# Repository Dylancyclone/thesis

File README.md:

# Building a Mobile Device that Leverages the Power of a Desktop Computer

## ASU Barrett Undergraduate Thesis 2022

## [READ THE PAPER HERE](./paper/small.pdf)

(Alternatively, [see it on asu.edu](https://keep.lib.asu.edu/items/165594))

Watch a timelapse of the paper here: https://youtu.be/VJ2HCxnmA_Y

## Abstract

With the recent focus of attention towards remote work and mobile computing, the possibility of taking a powerful workstation wherever needed is enticing.
However, even emerging laptops today struggle to compete with desktops in terms of cost, maintenance, and future upgrades.
The price point of a powerful laptop is considerably higher compared to an equally powerful desktop computer, and most laptops are manufactured in a way that makes upgrading parts of the machine difficult or impossible, forcing a complete purchase in the event of failure or a component needing an upgrade.

In the case where someone already owns a desktop computer and must be mobile, instead of needing to purchase a second device at full price, it may be possible to develop a low-cost computer that has just enough power to connect to the existing desktop and run all processing there, using the mobile device only as a user interface.

This thesis will explore the development of a custom PCB that utilizes a Raspberry Pi Computer Module 4, as well as the development of a fork of the Open Source project Moonlight to stream a host machine's screen to a remote client.
This implementation will be compared against other existing remote desktop solutions to analyze it's performance and quality.

## Information

This repository contains all the files and resources used to produce my Honors Thesis.

Folders are self-explanatory.

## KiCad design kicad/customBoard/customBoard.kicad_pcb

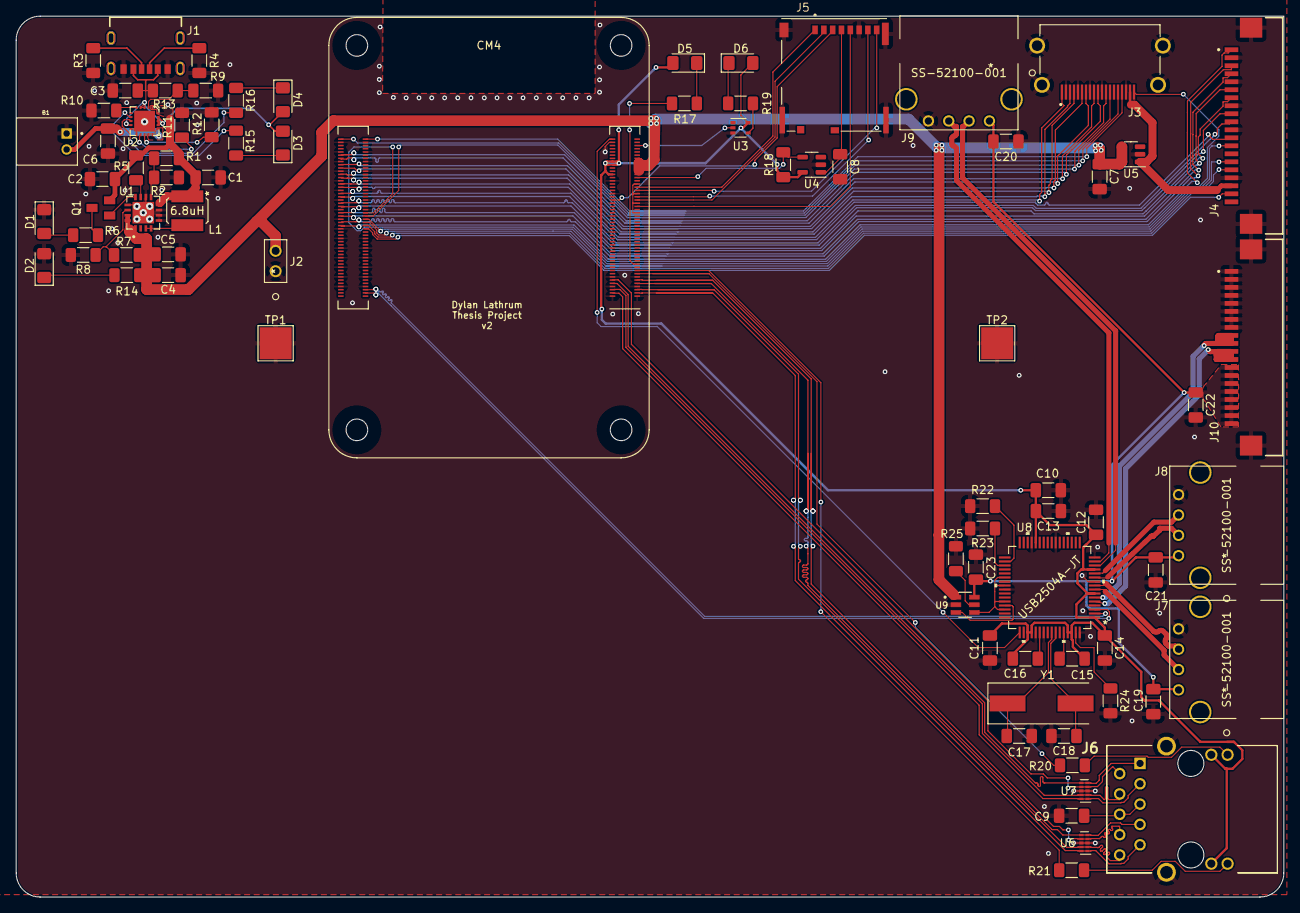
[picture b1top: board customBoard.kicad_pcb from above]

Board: 2 copper layers, 158.3 x 110.0 mm, 80 parts (0 on the bottom side), 98 nets.

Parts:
B1: JST 2-PH; JST_S2B-PH-K-S(LF)(SN)
C1, C3, C6: 10uF; C_1206_3216Metric_Pad1.33x1.80mm_HandSolder
C2: 0.1uF; C_1206_3216Metric_Pad1.33x1.80mm_HandSolder
C4: 2.2uF; C_1206_3216Metric_Pad1.33x1.80mm_HandSolder
C5, C23: 100uF; C_1206_3216Metric_Pad1.33x1.80mm_HandSolder
C7, C9, C12, C13, C14: 100n; C_1206_3216Metric_Pad1.33x1.80mm_HandSolder
C8, C10, C11, C19, C20, C21, C22: 10u; C_1206_3216Metric_Pad1.33x1.80mm_HandSolder
C15, C16: 4.7uF; C_1206_3216Metric_Pad1.33x1.80mm_HandSolder
C17, C18: 27pF; C_1206_3216Metric_Pad1.33x1.80mm_HandSolder
CM4: ComputeModule4-CM4; Raspberry-Pi-4-Compute-Module
D1, D2, D6: Red; LED_1206_3216Metric_Pad1.42x1.75mm_HandSolder
D3, D5: Green; LED_1206_3216Metric_Pad1.42x1.75mm_HandSolder
D4: Orange; LED_1206_3216Metric_Pad1.42x1.75mm_HandSolder
J1: USB4125-GF-A_REVA2; GCT_USB4125-GF-A_REVA2
J2: PREC002SAAN-RC
J3: SS-53000-001; STEWART_SS-53000-001
J4, J10: FFC3B07-20-T; GCT_FFC3B07-20-T
J5: Micro_SD_Card_Det; SDCARD_MOLEX_503398-1892
J6: ARJM11D7-502-AB-EW2; ARJM11D7502ABEW2
J7, J8, J9: SS-52100-001
L1: 6.8uH; NRS5030T6R8MMGJ
Q1: MMUN2133LT1G; SOT95P240X111-3N
R1, R7: 1.87M; R_1206_3216Metric_Pad1.30x1.75mm_HandSolder
R2: 340k; R_1206_3216Metric_Pad1.30x1.75mm_HandSolder
R3, R4: 5.1k; R_1206_3216Metric_Pad1.30x1.75mm_HandSolder
R5, R8: 200k; R_1206_3216Metric_Pad1.30x1.75mm_HandSolder
R6, R14, R17, R19: 1k; R_1206_3216Metric_Pad1.30x1.75mm_HandSolder
R9, R11: 100k; R_1206_3216Metric_Pad1.30x1.75mm_HandSolder
R10: 15k; R_1206_3216Metric_Pad1.30x1.75mm_HandSolder
R12: 1.0k; R_1206_3216Metric_Pad1.30x1.75mm_HandSolder
R13: 270k; R_1206_3216Metric_Pad1.30x1.75mm_HandSolder
R15, R16: 1K; R_1206_3216Metric_Pad1.30x1.75mm_HandSolder
R18: 12k 1%; R_1206_3216Metric_Pad1.30x1.75mm_HandSolder
R20, R21: 470R; R_1206_3216Metric_Pad1.30x1.75mm_HandSolder
R22, R23: 36K 1%; R_1206_3216Metric_Pad1.30x1.75mm_HandSolder
R24: 12K 1%; R_1206_3216Metric_Pad1.30x1.75mm_HandSolder
R25: 15K 1%; R_1206_3216Metric_Pad1.30x1.75mm_HandSolder
TP1, TP2: TestPoint; TestPoint_Pad_4.0x4.0mm
U1: TPS61090RSAR; QFN65P400X400X100-17N
U2: MCP73871-2CCI_ML; QFN-20-1EP_4x4mm_RevA
U3: 74LVC1G07; SOT-353_SC-70-5
U4: RT9742VGJ5; SOT-23-5
U5: RT9742ENGJ5; SOT-23-5
U6, U7: TPD4EUSB30; USON-10_2.5x1.0mm_P0.5mm
U8: USB2504A-JT
U9: AP22653W6-7; SOT95P280X145-6N
Y1: 24MHz; Crystal_SMD_HC49-SD

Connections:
+3V3: C10.1, C11.1, C12.1, C13.1, C14.1, C15.2, C16.2, CM4.78 (GPIO_VREF(1.8v/3.3v_Input)), CM4.84 (+3.3v_(Output)), CM4.86 (+3.3v_(Output)), D5.2 (A), D6.2 (A), J6.L1 (GREEN_A_1), J6.L3 (GREEN_A_2), R18.2, U3.5 (VCC), U4.5 (IN), U8.1 (VDDA33), U8.7 (VDDA33), U8.13 (VDDA33), U8.28 (VDD33), U8.51 (SELF_PWR), U8.52 (VBUS_DET), U8.61 (VDDA33PLL), U8.62 (ATEST/REG_EN)
/CM4/5v: C4.1, C5.1, C7.1, CM4.77 (+5v_(Input)), CM4.79 (+5v_(Input)), CM4.81 (+5v_(Input)), CM4.83 (+5v_(Input)), CM4.85 (+5v_(Input)), CM4.87 (+5v_(Input)), J2.2, R7.1, R14.2, U1.1 (VOUT), U1.15 (VOUT), U1.16 (VOUT), U5.4 (EN), U5.5 (IN), U9.1 (IN)
/CM4/ETH_LEDG: CM4.17 (Ethernet_nLED2(3.3v)), R21.1
/CM4/ETH_LEDY: CM4.15 (Ethernet_nLED3(3.3v)), R20.1
/CM4/HDMI0_CEC: CM4.151 (HDMI0_CEC), J3.13 (CEC)
/CM4/HDMI0_CK_N: CM4.190 (HDMI0_CLK_N), J3.12 (CK-)
/CM4/HDMI0_CK_P: CM4.188 (HDMI0_CLK_P), J3.10 (CK+)
/CM4/HDMI0_D0_N: CM4.184 (HDMI0_TX0_N), J3.9 (D0-)
/CM4/HDMI0_D0_P: CM4.182 (HDMI0_TX0_P), J3.7 (D0+)
/CM4/HDMI0_D1_N: CM4.178 (HDMI0_TX1_N), J3.6 (D1-)
/CM4/HDMI0_D1_P: CM4.176 (HDMI0_TX1_P), J3.4 (D1+)
/CM4/HDMI0_D2_N: CM4.172 (HDMI0_TX2_N), J3.3 (D2-)
/CM4/HDMI0_D2_P: CM4.170 (HDMI0_TX2_P), J3.1 (D2+)
/CM4/HDMI0_HOTPLUG: CM4.153 (HDMI0_HOTPLUG), J3.19 (HPD/HEAC-)
/CM4/HDMI0_SCL: CM4.200 (HDMI0_SCL), J3.15 (SCL)
/CM4/HDMI0_SDA: CM4.199 (HDMI0_SDA), J3.16 (SDA)
/CM4/HDMI1_CEC: CM4.149 (HDMI1_CEC), J4.13
/CM4/HDMI1_CK_N: CM4.166 (HDMI1_CLK_N), J4.12
/CM4/HDMI1_CK_P: CM4.164 (HDMI1_CLK_P), J4.10
/CM4/HDMI1_D0_N: CM4.160 (HDMI1_TX0_N), J4.9
/CM4/HDMI1_D0_P: CM4.158 (HDMI1_TX0_P), J4.7
/CM4/HDMI1_D1_N: CM4.154 (HDMI1_TX1_N), J4.6
/CM4/HDMI1_D1_P: CM4.152 (HDMI1_TX1_P), J4.4
/CM4/HDMI1_D2_N: CM4.148 (HDMI1_TX2_N), J4.3
/CM4/HDMI1_D2_P: CM4.146 (HDMI1_TX2_P), J4.1
/CM4/HDMI1_HOTPLUG: CM4.143 (HDMI1_HOTPLUG), J4.19
/CM4/HDMI1_SCL: CM4.147 (HDMI1_SCL), J4.15
/CM4/HDMI1_SDA: CM4.145 (HDMI1_SDA), J4.16
/CM4/HDMI_5v: J3.18 (+5V), J4.18, U5.1 (OUT)
/CM4/SD_CLK: CM4.57 (SD_CLK), J5.5 (CLK)
/CM4/SD_CMD: CM4.62 (SD_CMD), J5.3 (CMD)
/CM4/SD_DAT0: CM4.63 (SD_DAT0), J5.7 (DAT0)
/CM4/SD_DAT1: CM4.67 (SD_DAT1), J5.8 (DAT1)
/CM4/SD_DAT2: CM4.69 (SD_DAT2), J5.1 (DAT2)
/CM4/SD_DAT3: CM4.61 (SD_DAT3), J5.2 (DAT3/CD)
/CM4/TRD0_N: CM4.12 (Ethernet_Pair0_P), J6.2 (TRD1-), U7.4 (D2+)
/CM4/TRD0_P: CM4.10 (Ethernet_Pair0_N), J6.1 (TRD1+), U7.5 (D2-)
/CM4/TRD1_N: CM4.6 (Ethernet_Pair1_N), J6.4 (TRD2-), U7.2 (D1-)
/CM4/TRD1_P: CM4.4 (Ethernet_Pair1_P), J6.3 (TRD2+), U7.1 (D1+)
/CM4/TRD2_N: CM4.11 (Ethernet_Pair2_P), J6.8 (TRD3-), U6.4 (D2+)
/CM4/TRD2_P: CM4.9 (Ethernet_Pair2_N), J6.7 (TRD3+), U6.5 (D2-)
/CM4/TRD3_N: CM4.5 (Ethernet_Pair3_N), J6.10 (TRD4-), U6.2 (D1-)
/CM4/TRD3_P: CM4.3 (Ethernet_Pair3_P), J6.9 (TRD4+), U6.1 (D1+)
/CM4/USB2_N: CM4.103 (USB2_N), U8.3 (USBDN0)
/CM4/USB2_P: CM4.105 (USB2_P), U8.2 (USBDP0)
/CM4/nEXTRST: CM4.100 (nEXTRST), U8.49 (RESET_N)
/USB/D1_N: J10.11, J10.12, U8.5 (USBDN1)
/USB/D1_P: J10.9, J10.10, U8.6 (USBDP1)
/USB/D2_N: J7.2, U8.8 (USBDP2)
/USB/D2_P: J7.3, U8.9 (USBDN2)
/USB/D3_N: J8.2, U8.11 (USBDN3)
/USB/D3_P: J8.3, U8.12 (USBDP3)
/USB/D4_N: J9.2, U8.14 (USBDP4)
/USB/D4_P: J9.3, U8.15 (USBDN4)
/USB/OCS1: U8.38 (OCS4_N), U8.40 (OCS3_N), U8.44 (OCS2_N), U8.46 (OCS1_N), U9.4 (~FAULT)
/USB/VBUS: C19.1, C20.1, C21.1, C22.1, C23.1, J7.1, J8.1, J9.1, J10.13, J10.14, J10.15, J10.16, J10.17, J10.18, J10.19, J10.20, U9.6 (OUT)
GND: B1.1, C1.1, C2.1, C3.2, C4.2, C5.2, C6.2, C7.2, C8.2, C9.2, C10.2, C11.2, C12.2, C13.2, C14.2, C17.2, C18.2, C19.2, C20.2, C21.2, C22.2, C23.2, CM4.1 (GND), CM4.2 (GND), CM4.7 (GND), CM4.8 (GND), CM4.13 (GND), CM4.14 (GND), CM4.22 (GND), CM4.23 (GND), CM4.32 (GND), CM4.33 (GND), CM4.42 (GND), CM4.43 (GND), CM4.52 (GND), CM4.53 (GND), CM4.59 (GND), CM4.60 (GND), CM4.65 (GND), CM4.66 (GND), CM4.71 (GND), CM4.74 (GND), CM4.98 (GND), CM4.107 (GND), CM4.108 (GND), CM4.113 (GND), CM4.114 (GND), CM4.119 (GND), CM4.120 (GND), CM4.125 (GND), CM4.126 (GND), CM4.131 (GND), CM4.132 (GND), CM4.137 (GND), CM4.138 (GND), CM4.144 (GND), CM4.150 (GND), CM4.155 (GND), CM4.156 (GND), CM4.161 (GND), CM4.162 (GND), CM4.167 (GND), CM4.168 (GND), CM4.173 (GND), CM4.174 (GND), CM4.179 (GND), CM4.180 (GND), CM4.185 (GND), CM4.186 (GND), CM4.191 (GND), CM4.192 (GND), CM4.197 (GND), CM4.198 (GND), D1.1 (K), D2.2 (A), J1.A12 (GND), J1.B12 (GND), J2.1, J3.2 (D2S), J3.5 (D1S), J3.8 (D0S), J3.11 (CKS), J3.17 (GND), J3.S1 (SHIELD), J3.S2 (SHIELD), J3.S3 (SHIELD), J3.S4 (SHIELD), J4.2, J4.5, J4.8, J4.11, J4.17, J4.S1 (SHIELD), J4.S2 (SHIELD), J5.6 (VSS), J5.11 (SHIELD), J6.MH1, J6.MH2, J7.4, J8.4, J9.4, J10.1, J10.2, J10.3, J10.4, J10.5, J10.6, J10.7, J10.8, J10.S1 (SHIELD), J10.S2 (SHIELD), R2.2, R3.1, R4.1, R8.2, R9.2, R10.2, R11.2, R12.2, R22.2, R23.2, R24.2, R25.2, TP1.1, TP2.1, U1.5 (PGND), U1.6 (PGND), U1.7 (PGND), U1.10 (SYNC), U1.13 (GND), U1.17 (EXT_PAD), U2.10 (VSS), U2.11 (VSS), U2.21 (EP), U3.3 (GND), U4.2 (GND), U5.2 (GND), U6.3 (GND), U6.8 (GND), U7.3 (GND), U7.8 (GND), U8.4 (VSS), U8.10 (VSS), U8.16 (VSS), U8.23 (PRTPWR_POL), U8.29 (VSS), U8.41 (VSS), U8.53 (VSS), U8.55 (VSS), U8.64 (VSS), U9.2 (GND)
unnamed: B1.2, C6.1, U2.14 (VBAT), U2.15 (VBAT), U2.16 (VBAT_SENSE)
unnamed: C8.1, J5.4 (VDD), U4.1 (OUT)
unnamed: C9.1, J6.5 (TRCT1), J6.6 (TRCT2)
unnamed: C15.1, U8.60 (VDDA18PLL)
unnamed: C16.1, U8.54 (VDD18)
unnamed: C17.1, U8.57 (XTAL2), Y1.1
unnamed: C18.1, U8.58 (XTAL1/CLKIN), Y1.2
unnamed: D1.2 (A), R6.2
unnamed: D2.1 (K), R14.1
unnamed: D3.1 (K), R15.1
unnamed: D4.1 (K), R16.1
unnamed: D5.1 (K), R17.2
unnamed: D6.1 (K), R19.2
unnamed: J1.A5 (CC1), R4.2
unnamed: J1.B5 (CC2), R3.2
unnamed: J1.S1 (SHIELD), J1.S2 (SHIELD), J1.S3 (SHIELD), J1.S4 (SHIELD)
unnamed: J6.L2 (YELLOW_K_1), R21.2
unnamed: J6.L4 (YELLOW_K_2), R20.2
unnamed: L1.2, U1.3 (SW), U1.4 (SW)
unnamed: CM4.21 (PI_nLED_Activity), R17.1
unnamed: CM4.75 (SD_PWR_ON), R18.1, U4.4 (EN)
unnamed: CM4.95 (nPI_LED_PWR), U3.2
unnamed: Q1.1 (B), U1.12 (LBO)
unnamed: Q1.3 (C), R6.1
unnamed: R1.2, R2.1, U1.9 (LBI)
unnamed: R5.1, U1.11 (EN)
unnamed: R7.2, R8.1, U1.14 (FB)
unnamed: R10.1, U2.5 (THERM)
unnamed: R11.1, U2.12 (PROG3)
unnamed: R12.1, U2.13 (PROG1)
unnamed: R9.1, R13.1, U2.2 (VPCC)
unnamed: R15.2, U2.7 (STAT2)
unnamed: R16.2, U2.8 (STAT1/~LBO)
unnamed: R19.1, U3.4
unnamed: R22.1, U8.34 (SDA/SMBDATA)
unnamed: R23.1, U8.35 (SCL/SMBCLK)
unnamed: R24.1, U8.63 (RBIAS)
unnamed: R25.1, U9.5 (ILIM)
unnamed: U8.45 (PRTPWR1), U9.3 (EN)
VBAT: C1.2, C2.2, L1.1, Q1.2 (E), R1.1, R5.2, U1.8 (VBAT), U2.1 (OUT), U2.20 (OUT)
VBUS: C3.1, D3.2 (A), D4.2 (A), J1.A9 (VBUS), J1.B9 (VBUS), R13.2, U2.3 (SEL), U2.4 (PROG2), U2.9 (~TE), U2.17 (CE), U2.18 (IN), U2.19 (IN)

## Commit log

2021-05-06 Start prospectus document
    Here we go!
    I'm not entirely sure what's needed for the prospectus document, but this starts filling out information based off of what was in the given example. I've sent an email to set up a meeting with my dir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
2021-05-23 Prepare file structure
    These are the folders I think I'll be using throughout the project, and since I'm thinking about splitting up work between branches, it would be useful to have a basic structure in place visually to 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
    I'm still not certain how the branches will work out
2021-05-24 Fix typo and experiment with latex editing formatting
    It's a little awkward to write regular text into VSCode
2021-05-25 Start working on the preliminary bill of materials
    All funding needs to be preapproved, even though the funds are distributed through reimbursement. This means even though nothing has been purchased, and I will have to purchase everything on my own, 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
2021-05-26 Set up KiCAD
    Initializes the project and load Digi-Key libraries
2021-06-01 Rework BOM for power supply
    Instead of basing the power supply off of the Aegis project, I'm instead looking at Adafruit's Powerboost 1000C and trying to build something similar to that
2021-06-04 Continue working on BOM for primary board systems
    Next up is things like the peripherals and other purchases
2021-06-07 Finish initial draft of pcb BOM
    Because I don't have much experience with PCB making, I've been trying to estimate what I'll need for this project to work so I can submit the funding application for pre-approval. Since everything h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
    So what I've done is compiled a potential list, and once funding is approved I will order the basic materials like the io board so I can get my hands on the cm4 and then redesign probably redesign ev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
    Note this isn't the final BOM that will be submitted be
2021-06-07 Enter in quantities for BOM
2021-06-07 Update prospectus to include PCB plan
2021-06-09 Tweak prospectus schedule
2021-06-09 Tweak BOM and export as PDF
    Since the funding application doesn't accept excel sheets, the main sheet has been saved as a pdf for ease of uploading. I think everything is ready to submit as soon as the application opens
2021-07-30 Funding Approved!
    Huzzah! The funding application has been application has been approved! I've download a copy of the receipt for records and will merge this in now that it is fully resolved. I think I'll keep record 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
2021-08-02 Add receipt from microcenter and create tracking spreadsheet
    So I wanted to try out some fancy excel work, it should be mostly in place until a second receipt is added. I spent a little too much time on that
2021-08-03 Add receipt from pine64
    I think this spreadsheet will be cool
2021-08-30 First draft of the power circuit
    While this is my first time developing any kind of PCB, this circuit is pretty similar to an existing schematic, so it should be pretty solid.
2021-09-09 First draft of CM4_GPIO
    The CM4 connectors are split into two units. This is the right unit, name GPIO. Next is the left, High Speed Serial unit.
2021-09-23 Add receipt from Walmart
    Both the CM4IO and the Pinecil use a 12V barrel jack for power
2021-09-23 Add details from Amazon purchase
    The purchase has been made, but I know I have to wait for the invoice to say shipped before I can add the receipt. Also reorganized the groups in the spreadsheet so the name and total amount are alwa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
2021-09-25 Draft CM4 High Speed Serial
    One interesting dilemma that has come up is how to handle replacements for the RT9742 part. Since the ones I was originally going to use are out of stock, an exciting hunt occurred to find a replacem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
2021-09-27 Add receipts from Amazon purchase
    They've now shipped
2021-10-02 First draft of USB
    This should complete the first draft of the schematic!
    Now time to design the PCB itself
2021-10-04 Generate Netlist
2021-10-10 First Draft of Power PCB
2021-10-11 Rework Power PCB and draft SD
    Moving things around so they would make sense on the final board. Flipped around some of the power circuit so the battery can be plugged in on the left side to make room for all the ports on the righ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
2021-10-11 Save progress on USB
2021-10-12 Draft HDMI and more differential pairs
2021-10-12 Draft before fixing errors
2021-10-12 Fix errors with draft
    Now I need to run it by a bunch of people, but from my point of view, I don't know what else to do before the fabrication step
2021-10-22 Updates based on meeting with Dr. Jordan
    Everything should be good to go now, next up is generating a bill of materials (making sure everything is in stock), and generating gerbers
2021-10-24 Generate BOM
    Clean up all the part data and add manufacturer's numbers for ordering
2021-10-24 Generate Gerbers
    Off to JLCPCB!
2021-10-24 Add receipts for ordering first draft of PCB
    Unfortunately Digi-key hasn't provided a receipt yet, so hopefully that'll come soon. Also doesn't include order from heisener since I need to wait for a quote
2021-10-25 Add reciepts from Digikey
    The invoices have been generated. Still waiting to hear from Heisener
2021-11-02 Add receipts for Digikey, LCSC, and TI, and revamp cumulative calculation
2021-11-04 Initialize code directory
    Create folders for the forked moonlight code, the arm image profile data, and scripts to automate everything. Everything is subject to change since technically a lot of this can only be run on a manj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
2021-11-04 Update setup script to set up development environment and imaging environment
2021-11-10 Create build toolchain Automate the steps to build, package, and create the installable image
2021-11-10 Add XFCE and start testing compiling on WSL2
2021-11-11 Save tweaks to build process
2021-12-31 Update config.txt for new screen
2022-01-08 Add reciepts from Amazon
    MicroSD card and 7" Display
2022-01-09 Add windows logger
    In order to record the latency of the program, this will log when keys are pressed on the windows machine. Next is to write the same program for linux, so the times can be compared
2022-01-09 Add color changing log to windows logger
    It's great to know when the inputs are registered, but what about when the actual screen updates? This is how we can check when the client recieves the new data from the server, since the server isn'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
2022-01-09 Create Web portion of the data logger
    The simple page will just switch colors every time a key is pressed in a way that is super easy to see from the client and server side
2022-01-09 Create Linux logger This is the client side of the data logger, still need to add the color detection like on windows
2022-01-09 Add color changing log to Linux Now the client can record when it recieves the update from the server. Theoretically, data can now be collected!
2022-01-09 Comment out Terminal logging and add a little documentation
2022-01-13 Add Stats logging to moonlight
2022-01-13 Save ibom
    I generated this awhile ago, but for some reason never actually committed it
2022-01-15 Load LaTeX template
    This template is based on a template by:
    Steve Gunn (http://users.ecs.soton.ac.uk/srg/softwaretools/document/templates/)
    Sunil Patel (http://www.sunilpatel.co.uk/thesis-template/)
    Template license:
    CC BY-NC-SA 3.0 (http://creativecommons.org/licenses/by-nc-sa/3.0/)
2022-01-15 Fill out basic information in template
    Just to get the basic variables filled in
2022-01-19 Add additional info to datalogger
2022-01-19 Record keys and colors seperately
2022-01-19 Record first points of data
    All of this is subject to change as I don't really know the best way to do this. What I've record so far is the input delay for the moonlight application determined by the delay in keystrokes and col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
2022-01-26 Record data under ideal conditions
    Next up is to record while the GPU is under full load
2022-01-26 Record GPU-stressed data
2022-01-26 Record CPU-stressed data
2022-01-27 First draft of outline
    This also creates the file structure for each of the chapters, which is nice
2022-01-31 Version 2 of board
    Fix U2 to use the footprint "QFN-20-1EP_4x4mm_RevA" instead of "QFN-20-1EP_4x4mm"
    Rotate J5 by 180 degrees
    Slight aesthetic tweaks
2022-01-31 Rename KiCAD project
2022-01-31 Generate v2 gerbers and BOM
2022-02-01 Begin working on the Background section
    The first words are always the hardest
2022-02-08 Draft of background section
2022-02-17 Feedback from Advisor
    Mostly just notes, they will be fixed next
2022-02-22 Fix comments for Background chapter
2022-02-22 Start State of the Art chapter
2022-02-23 Feedback from advisor
2022-02-26 Add receipts from jlcpcb and amazon for v2 board
2022-02-26 Fix cumulative stats being off
    thanks excel
2022-03-12 Draft State of the Art Chapter
    I need to pick up the pace
2022-03-15 Start working on the Hardware chapter
2022-03-16 Draft prototyping sections
    The next section is going to be meaty, it might need to be broken up somehow
2022-03-19 Change first person to third person in Hardware chapter
2022-03-22 Appendix A and B
2022-03-24 Fix feedback issues and start Design PCB section
2022-03-25 Designing the power, usb, hdmi and start cm4 circuits
2022-03-29 Tweaks and updates to the hardware sections
    Now a nice big sprint can begin. Just need the time
2022-03-29 Add thesis defense announcement
2022-03-30 (almost) finish draft of hardware section
    Still need to investigate the USB issues and maybe add more detail to the end of the chapter, but other than that I have a couple of questions to resolve then I'm happyish with the chapter
2022-03-30 Start the software section
2022-03-31 Fixes from feedback, add images of physical board
2022-04-01 Start developing for ARM section
2022-04-02 Finish draft of software section
2022-04-03 Start Evaluation section, add graphs
2022-04-04 Continue evaluation chapter
2022-04-04 Finish draft of evaluation chapter
2022-04-05 Draft Intro and Conclusion chapters
2022-04-05 Prepare Complete (not final) draft
    This draft will be sent of to each of the committee members to read through before the thesis defense.
    The PDF has been rendered in "final" mode, so no comments will show through.
    small.pdf is a compressed version of the main pdf, with no differences except each of the images have been compressed to 300dpi.
2022-04-08 First version of the presentation
    Funny, the defense is tomorrow. This should've been done by now. All well, this whole thing is a time crunch.
2022-04-08 Fix footprint image being incorrect
    haha they were so similar I even mixed them up here
2022-04-08 Fix inconsistencies in presentation, add resource pictures
2022-04-13 Feedback from advisor and thesis defense
2022-04-14 Updates based on committee feedback
2022-04-16 Rework linux datalogger and add autotyping tool
    This allows the testing to be automated and exact rather than based on human inperfection
2022-04-20 Rewrite Data logger again for more consistent output
    Also fix that annoying bug that caused the windows logger to randomly slow the entire computer to a crawl if left on too long
2022-04-24 Record new data and update evaluation chapter
2022-04-24 Write real world evaluation section
2022-04-24 Implement Director feedback
    Everything except for summaries for each section and a last look-over
2022-04-25 Add summaries
2022-04-26 Changes from feedback
    Almost done
2022-04-26 Clarify latency section and prepare for submission
    This is the last thing that needed to be tweaked before the thesis is finalized
2022-04-26 Switch back to two sided for printing
    The thesis has been submitted!
2022-05-04 Fix problem receipts
    Some receipts were not accepted by the billing office,
2022-05-24 Add notes for usb controller
2022-10-01 Update readme with links to timelapse
    The timelapse was created using the following project: https://github.com/Dylancyclone/EvolutionThesis

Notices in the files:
parts and their libraries:
Copyright 2021 Accelerated Designs. All rights reserved.
